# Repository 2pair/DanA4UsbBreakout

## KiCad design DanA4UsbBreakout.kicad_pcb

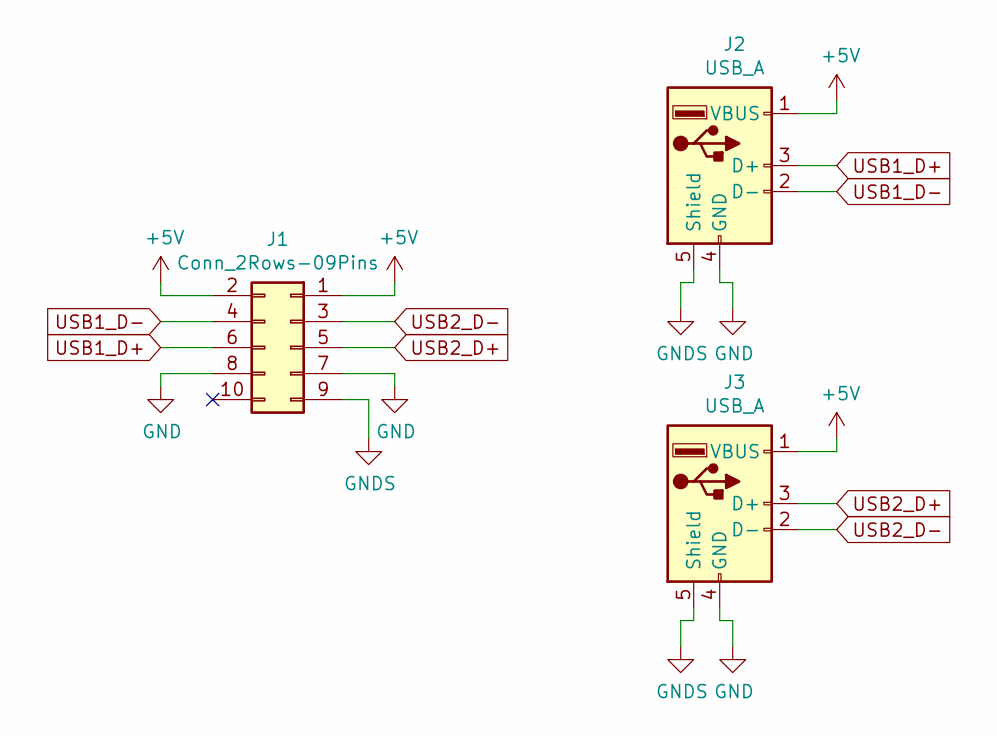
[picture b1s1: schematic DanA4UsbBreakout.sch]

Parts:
J1: Conn_2Rows-09Pins; Harwin_2x5_female_header_M20-7920542R
J2, J3: USB_A; Wurth_USB-A_629104190121

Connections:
+5V: J1.1, J1.2, J2.1 (VBUS), J3.1 (VBUS)
GND: J1.7, J1.8, J2.4 (GND), J3.4 (GND)
GNDS: J1.9, J2.5 (Shield), J3.5 (Shield)
USB1_D+: J1.6, J2.3 (D+)
USB1_D-: J1.4, J2.2 (D-)
USB2_D+: J1.5, J3.3 (D+)
USB2_D-: J1.3, J3.2 (D-)

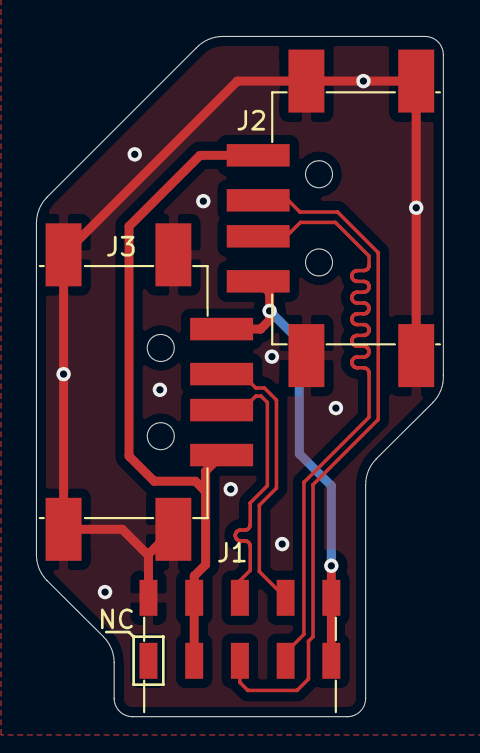
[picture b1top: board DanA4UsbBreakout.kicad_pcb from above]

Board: 2 copper layers, 22.6 x 37.8 mm, 3 parts (0 on the bottom side), 7 nets.

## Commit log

2020-10-16 The rest of the owl
2020-10-16 updated gitignore, added potentially useful files
    *-cache.lib might be useful if the actually library every gets changed, although we only have custom components so probably not an issue. gbrjob might be useful for production but isn't strictly need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
